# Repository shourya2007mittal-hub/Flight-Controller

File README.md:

# Flight Controller

I am making a STM32F405RGT6 based flight controller for my drone.and has IMU and barometer and has a USB-B Type. It is designed for 4 motor drone. It has 4 layer PCB
<br>

<br>

## Features

Microcontroller: STM32F405RGT6<br>
IMU Sensor: MPU-6050 / ICM-2098<br>
Barometer: BMP280<br>

- ## Bill of Materials (BOM)
| Serial Num | Description | Total (USD) | 
|----:|--------------------------|-------------|
| 1  | PCB and Assembly  |167.50 |
| 2 | Shipping - Discount JLCPCB  |14.55 |

### 💰 Cost Summary

- **Estimated Total Cost ( PCB ASSEMBLY + Shipping):** **$182.05 USD**
 ## Schematic & PCB<br>

<br>

# 3d Render<br>

  <br>

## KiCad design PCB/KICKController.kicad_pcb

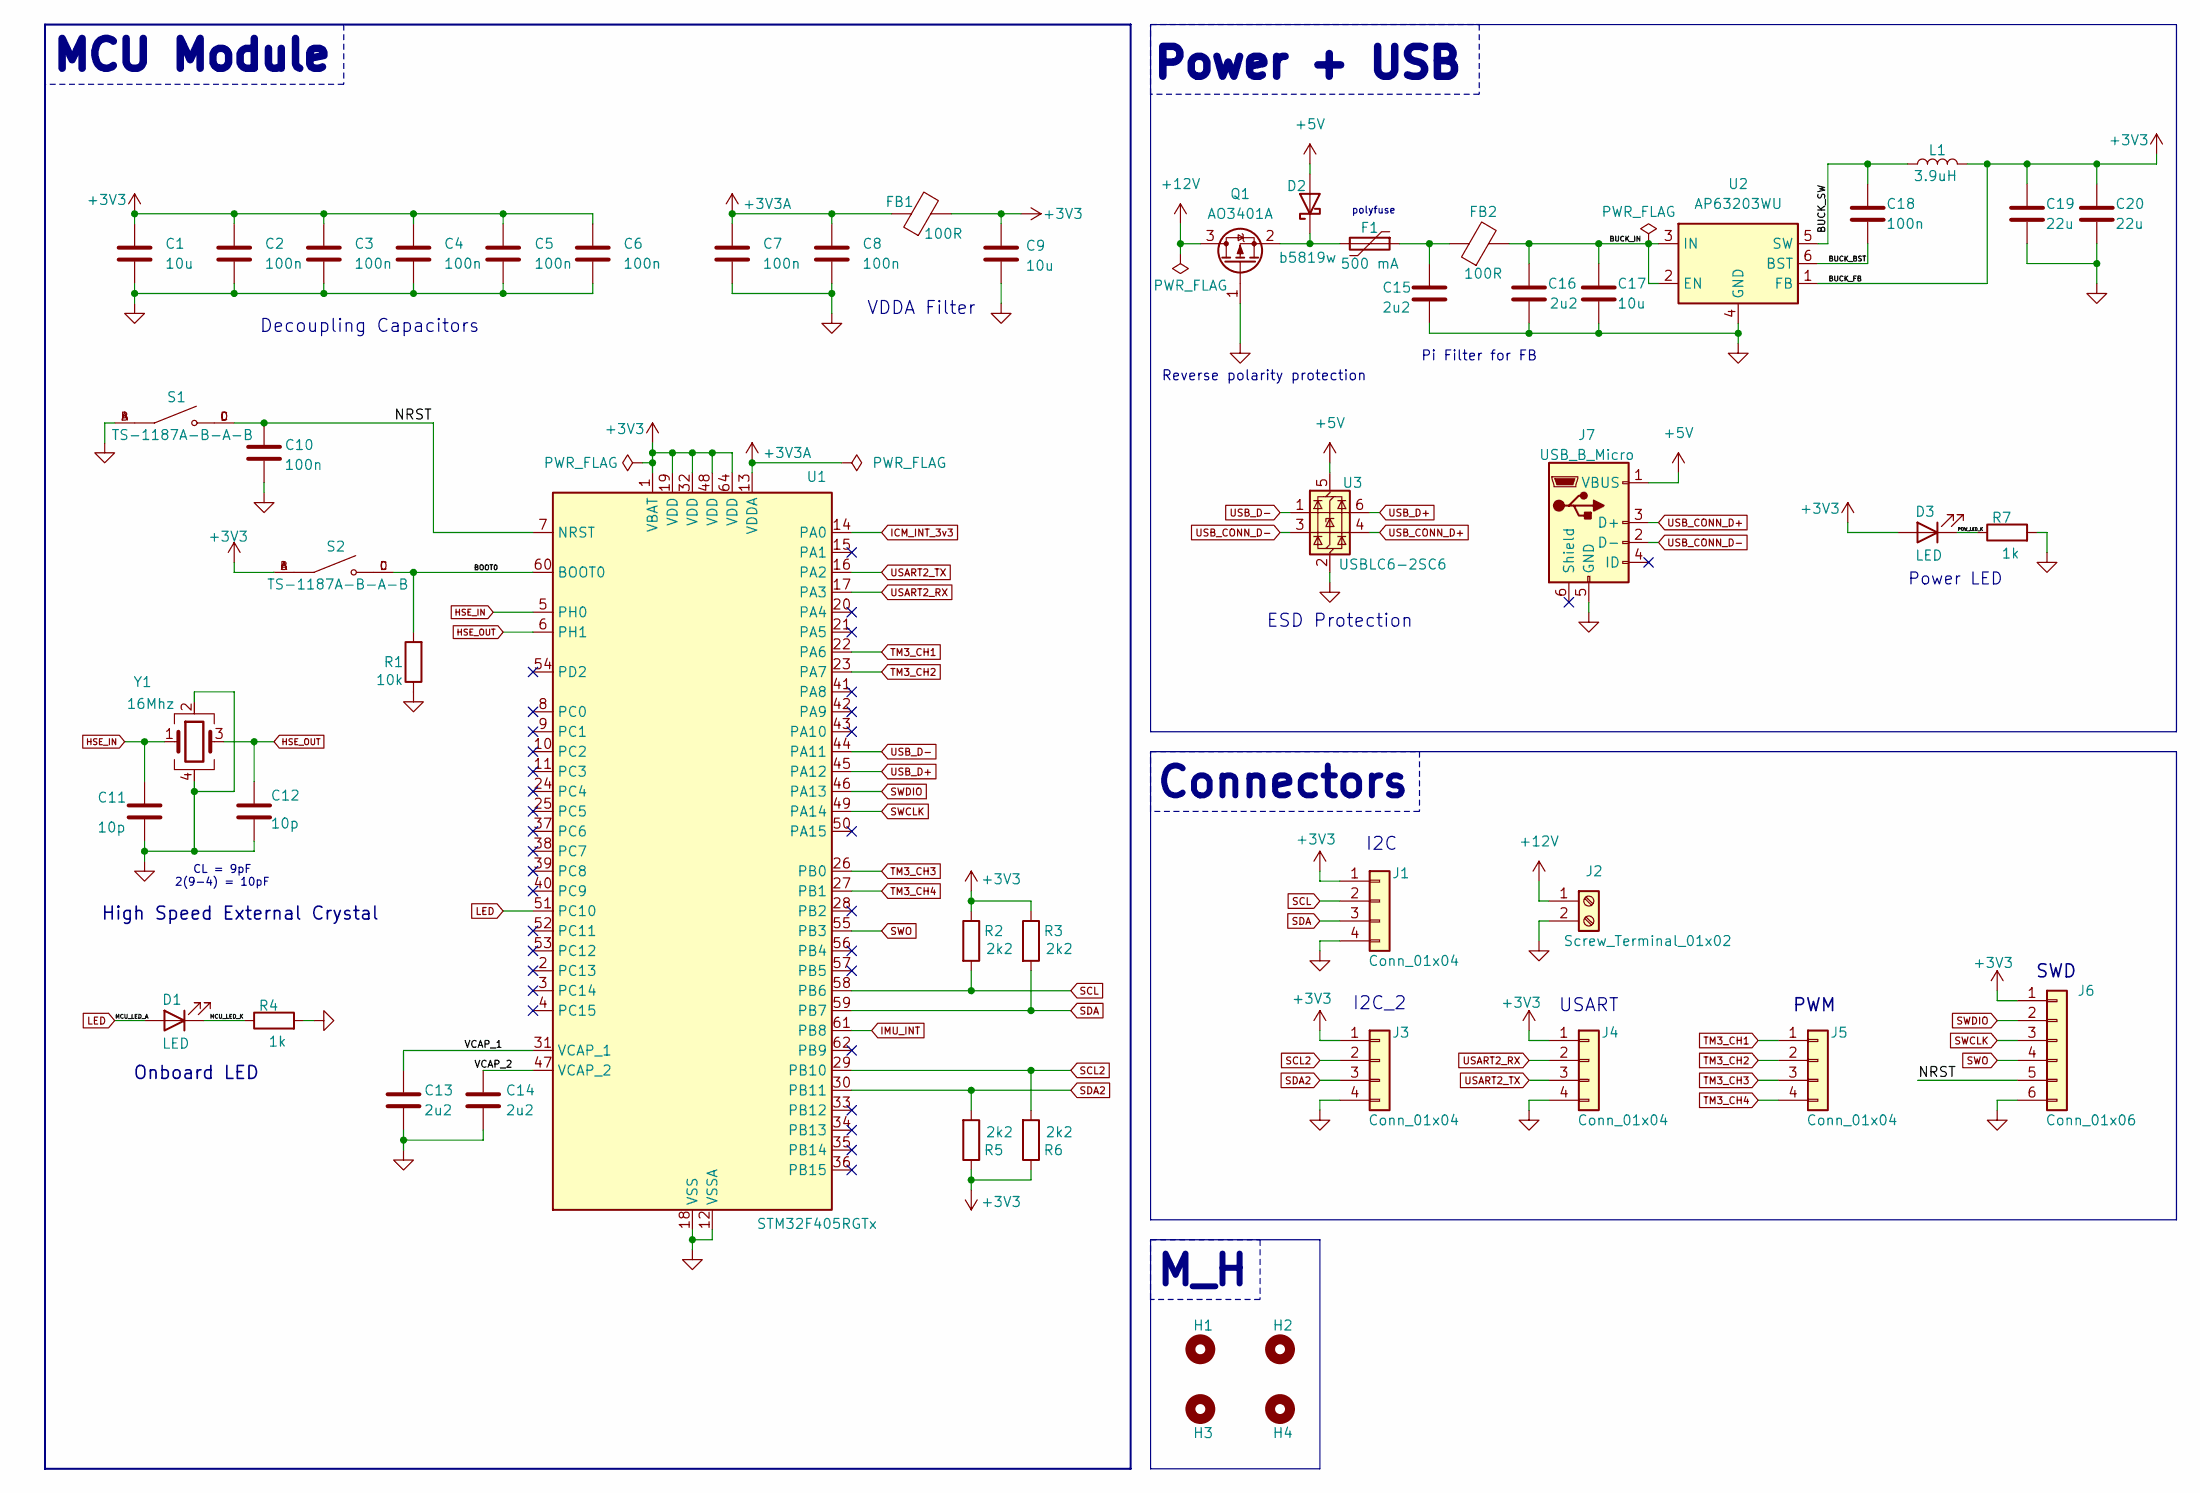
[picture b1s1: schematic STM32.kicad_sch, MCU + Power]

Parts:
C1, C9, C17: 10u; C_0603_1608Metric
C2, C3, C4, C5, C6, C7, C8, C10: 100n; C_0402_1005Metric
C11, C12: 10p; C_0603_1608Metric
C13, C14, C15, C16: 2u2; C_0603_1608Metric
C18: 100n; C_0805_2012Metric
C19, C20: 22u; C_0805_2012Metric
D1, D3: LED; LED_0603_1608Metric
D2: b5819w; D_SOD-123
F1: 500 mA; Fuse_0603_1608Metric
FB1, FB2: 100R; L_0805_2012Metric
H1, H2, H3, H4: MountingHole; MountingHole_4.3mm_M4_Pad_Via
J1, J3, J4, J5: Conn_01x04; PinSocket_1x04_P2.54mm_Vertical
J2: Screw_Terminal_01x02; TerminalBlock_Xinya_XY308-2.54-2P_1x02_P2.54mm_Horizontal
J6: Conn_01x06; PinSocket_1x06_P2.54mm_Vertical
J7: USB_B_Micro; USB_Micro-B_Amphenol_10118193-0001LF_Horizontal
L1: 3.9uH; L_Sunlord_SWPA4030S
Q1: AO3401A; SOT-23
R1: 10k; R_0603_1608Metric
R2, R3, R5, R6: 2k2; R_0603_1608Metric
R4, R7: 1k; R_0603_1608Metric
S1, S2: TS-1187A-B-A-B; SW_TS-1187A-B-A-B; PARTREV A0
U1: STM32F405RGTx; LQFP-64_10x10mm_P0.5mm
U2: AP63203WU; TSOT-23-6
U3: USBLC6-2SC6; SOT-23-6
Y1: 16Mhz; Crystal_SMD_3225-4Pin_3.2x2.5mm

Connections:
+3V3: C1.1, C2.1, C3.1, C4.1, C5.1, C6.1, C9.1, C19.1, C20.1, D3.2 (A), FB1.2, J1.1, J3.1, J4.1, J6.1, L1.2, R2.1, R3.1, R5.1, R6.1, S2.A, S2.B, U1.1 (VBAT), U1.19 (VDD), U1.32 (VDD), U1.48 (VDD), U1.64 (VDD), U2.1 (FB); also elsewhere on the board
+3V3A: C7.1, C8.1, FB1.1, U1.13 (VDDA)
+5V: D2.2 (A), J7.1 (VBUS), U3.5 (VBUS)
+12V: J2.1, Q1.3 (D)
/STM32/BOOT0: R1.2, S2.C, S2.D, U1.60 (BOOT0)
/STM32/BUCK_BST: C18.2, U2.6 (BST)
/STM32/BUCK_IN: C16.1, C17.1, FB2.2, U2.2 (EN), U2.3 (IN)
/STM32/BUCK_SW: C18.1, L1.1, U2.5 (SW)
/STM32/MCU_LED_K: D1.1 (K), R4.1
/STM32/NRST: C10.1, J6.5, S1.C, S1.D, U1.7 (NRST)
/STM32/POW_LED_K: D3.1 (K), R7.1
/STM32/VCAP_1: C13.1, U1.31 (VCAP_1)
/STM32/VCAP_2: C14.1, U1.47 (VCAP_2)
GND: C1.2, C2.2, C3.2, C4.2, C5.2, C6.2, C7.2, C8.2, C9.2, C10.2, C11.2, C12.2, C13.2, C14.2, C15.2, C16.2, C17.2, C19.2, C20.2, H1.1, H2.1, H3.1, H4.1, J1.4, J2.2, J3.4, J4.4, J6.6, J7.5 (GND), Q1.1 (G), R1.1, R4.2, R7.2, S1.A, S1.B, U1.12 (VSSA), U1.18 (VSS), U1.63 (VSS), U2.4 (GND), U3.2 (GND), Y1.2, Y1.4; also elsewhere on the board
HSE_IN: C11.1, U1.5 (PH0), Y1.1
HSE_OUT: C12.1, U1.6 (PH1), Y1.3
ICM_INT_3v3: U1.14 (PA0); also elsewhere on the board
IMU_INT: U1.61 (PB8); also elsewhere on the board
LED: D1.2 (A), U1.51 (PC10)
unnamed: C15.1, F1.1, FB2.1
unnamed: D2.1 (K), F1.2, Q1.2 (S)
SCL: J1.2, R2.2, U1.58 (PB6); also elsewhere on the board
SCL2: J3.2, R6.2, U1.29 (PB10); also elsewhere on the board
SDA: J1.3, R3.2, U1.59 (PB7); also elsewhere on the board
SDA2: J3.3, R5.2, U1.30 (PB11); also elsewhere on the board
SWCLK: J6.3, U1.49 (PA14)
SWDIO: J6.2, U1.46 (PA13)
SWO: J6.4, U1.55 (PB3)
TM3_CH1: J5.1, U1.22 (PA6)
TM3_CH2: J5.2, U1.23 (PA7)
TM3_CH3: J5.3, U1.26 (PB0)
TM3_CH4: J5.4, U1.27 (PB1)
USART2_RX: J4.2, U1.17 (PA3)
USART2_TX: J4.3, U1.16 (PA2)
USB_CONN_D+: J7.3 (D+), U3.4 (I/O2)
USB_CONN_D-: J7.2 (D-), U3.3 (I/O2)
USB_D+: U1.45 (PA12), U3.6 (I/O1)
USB_D-: U1.44 (PA11), U3.1 (I/O1)

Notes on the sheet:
polyfuse
ESD Protection
Decoupling Capacitors
CL = 9pF 2(9-4) = 10pF
VDDA Filter
Onboard LED
USART
M_H
Pi Filter for FB
I2C
SWD
High Speed External Crystal
Power LED
PWM
Reverse polarity protection
MCU Module
Connectors
Power + USB
I2C_2

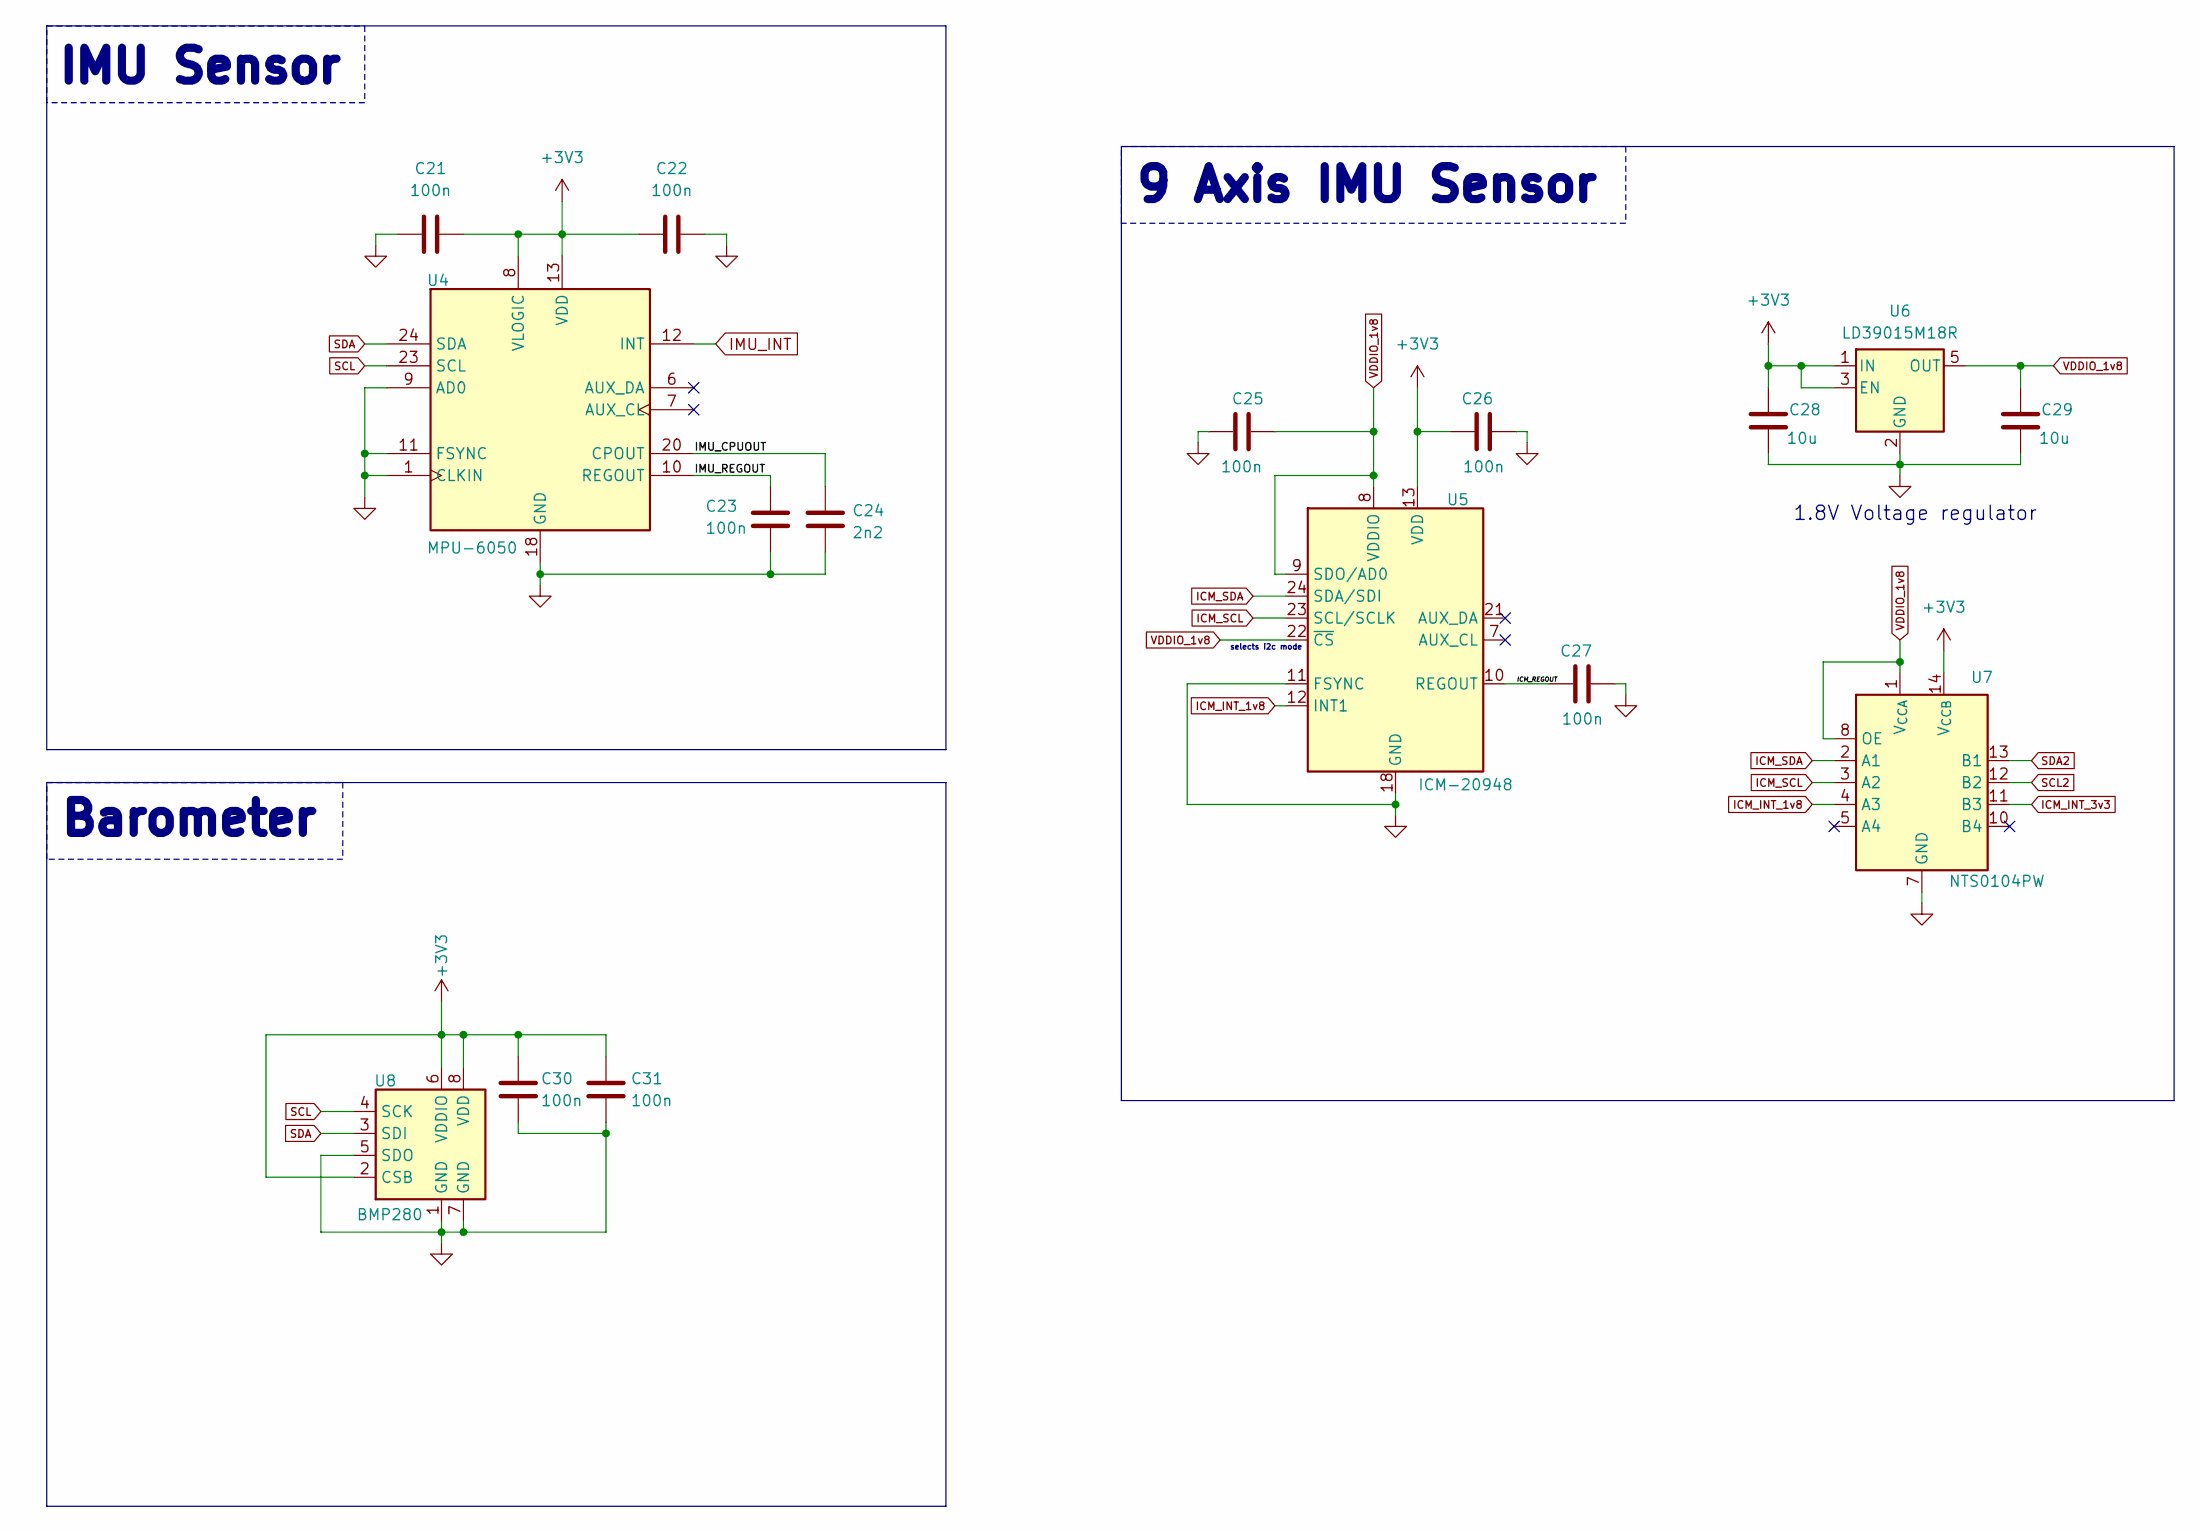
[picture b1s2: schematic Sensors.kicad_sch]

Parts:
C21, C22, C23, C25, C26, C27, C30, C31: 100n; C_0402_1005Metric
C24: 2n2; C_0603_1608Metric
C28, C29: 10u; C_0603_1608Metric
U4: MPU-6050; InvenSense_QFN-24_4x4mm_P0.5mm
U5: ICM-20948; InvenSense_QFN-24_3x3mm_P0.4mm
U6: LD39015M18R; SOT-23-5
U7: NTS0104PW; TSSOP-14_4.4x5mm_P0.65mm
U8: BMP280; Bosch_LGA-8_2x2.5mm_P0.65mm_ClockwisePinNumbering

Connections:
+3V3: C21.2, C22.1, C26.1, C28.1, C30.1, C31.2, U4.8 (VLOGIC), U4.13 (VDD), U5.13 (VDD), U6.1 (IN), U6.3 (EN), U7.14 (V_{CCB}), U8.2 (CSB), U8.6 (VDDIO), U8.8 (VDD); also elsewhere on the board
/Sensors/ICM_REGOUT: C27.1, U5.10 (REGOUT)
/Sensors/IMU_CPUOUT: C24.1, U4.20 (CPOUT)
/Sensors/IMU_REGOUT: C23.1, U4.10 (REGOUT)
GND: C21.1, C22.2, C23.2, C24.2, C25.2, C26.2, C27.2, C28.2, C29.2, C30.2, C31.1, U4.1 (CLKIN), U4.9 (AD0), U4.11 (FSYNC), U4.18 (GND), U5.11 (FSYNC), U5.18 (GND), U5.20 (GND), U6.2 (GND), U7.7 (GND), U8.1 (GND), U8.5 (SDO), U8.7 (GND); also elsewhere on the board
ICM_INT_1v8: U5.12 (INT1), U7.4 (A3)
ICM_INT_3v3: U7.11 (B3); also elsewhere on the board
ICM_SCL: U5.23 (SCL/SCLK), U7.3 (A2)
ICM_SDA: U5.24 (SDA/SDI), U7.2 (A1)
IMU_INT: U4.12 (INT); also elsewhere on the board
SCL: U4.23 (SCL), U8.4 (SCK); also elsewhere on the board
SCL2: U7.12 (B2); also elsewhere on the board
SDA: U4.24 (SDA), U8.3 (SDI); also elsewhere on the board
SDA2: U7.13 (B1); also elsewhere on the board
VDDIO_1v8: C25.1, C29.1, U5.8 (VDDIO), U5.9 (SDO/AD0), U5.22 (~CS), U6.5 (OUT), U7.1 (V_{CCA}), U7.8 (OE)

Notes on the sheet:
9 Axis IMU Sensor
1.8V Voltage regulator
IMU Sensor
Barometer
selects i2c mode

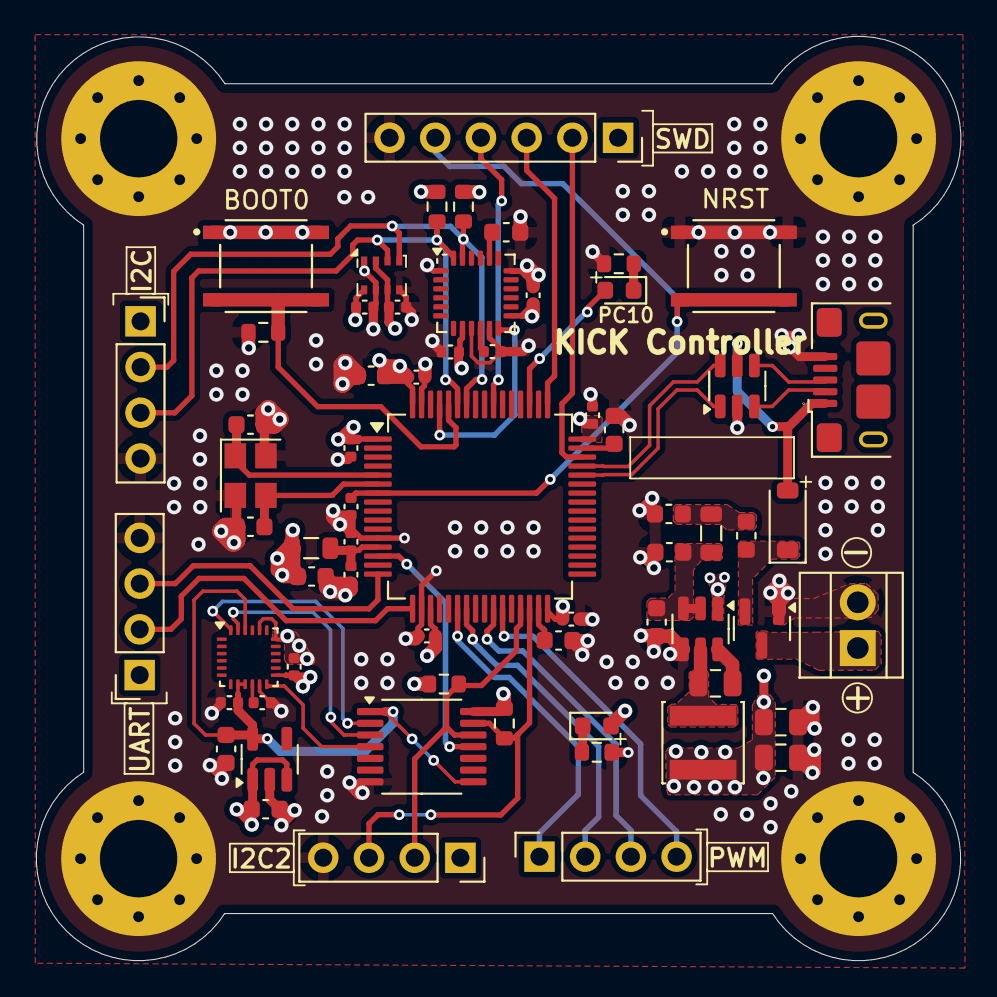
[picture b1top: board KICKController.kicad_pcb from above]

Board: 4 copper layers, 51.4 x 51.3 mm, 68 parts (0 on the bottom side), 45 nets.
